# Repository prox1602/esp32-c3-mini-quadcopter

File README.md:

# ESP32-C3 Mini Quadcopter

> **Project Status: Work in Progress**  
> Custom PCB (Rev 1.0), 3D-printed airframe, and final hardware assembly are complete. Firmware development is currently paused halfway through to finalize the ESP-NOW communication protocol with the custom handheld controller.

A lightweight, custom-built mini quadcopter engineered from scratch — covering KiCad PCB design, discrete MOSFET motor drivers, 3D-printed mechanics, and modular C++ flight firmware built around the **Seeed Studio XIAO ESP32-C3**.

---

## Development Story & Design Goals

The primary goal of this project was simple: **design a compact, custom-built quadcopter from the ground up and get it flying**, moving beyond off-the-shelf flight controllers into custom PCB design and ECAD–MCAD integration.

* **Scope & MCU Trade-off:** Early in the concept phase, I considered adding a small onboard camera for video recording. However, because the **ESP32-C3** is a single-core RISC-V microcontroller, handling real-time flight stabilization alongside video streaming/recording would compromise control loop reliability. I deliberately narrowed the scope to focus purely on flight control and low-latency wireless communication via **ESP-NOW**.
* **ECAD–MCAD Workflow:** This was my first project integrating a custom KiCad board directly into an Autodesk Inventor mechanical assembly (`cad/drone_assembly.stp`) to verify mounting clearances, motor spacing, wire routing channels, and canopy fit before 3D printing.

---

## Hardware Architecture & Bill of Materials

The propulsion stage uses four discrete low-side N-channel MOSFET switches integrated directly onto the custom PCB. Each channel includes an **SS14** Schottky flyback diode to suppress inductive voltage spikes and a **10 kΩ** gate pull-down resistor to prevent unintended motor spin-up during boot. A **470 µF** bulk electrolytic capacitor sits across the battery rail to mitigate voltage sag under load.

| Component | Specification | Qty | Role |
| :--- | :--- | :---: | :--- |
| **Microcontroller** | Seeed Studio XIAO ESP32-C3 (RISC-V, 3.3V) | 1 | Flight controller & ESP-NOW wireless link |
| **IMU Sensor** | GY-BMI160 (6-axis accel + gyro, I2C) | 1 | Attitude and angular rate estimation |
| **Motors** | 8520 Coreless Brushed DC (8.5 × 20 mm, CW/CCW) | 4 | Quadcopter propulsion |
| **Motor Drivers** | AO3400A N-MOSFET (SOT-23, 30V / 5.8A, 1.4W) | 4 | Logic-level PWM motor switching |
| **Flyback Protection** | SS14 Schottky Diode (SMB package) | 4 | Inductive spike suppression across motors |
| **Gate Pull-downs** | 10 kΩ Resistors (`R1`–`R4`) | 4 | Keep MOSFET gates low during MCU reset |
| **Bulk Decoupling** | 470 µF Electrolytic Capacitor (`C1`) | 1 | Stabilize 1S LiPo rail during current spikes |
| **Battery** | 1S LiPo 3.7V 600 mAh (30C discharge) | 1 | Main power supply |
| **Airframe & Canopy** | Custom 3D-printed frame & electronics cover | 1 set | Mechanical structure & PCB protection |

---

## Rev 1.0 Errata & Lessons Learned

This board is my **first custom PCB designed in KiCad**. Bringing up Rev 1.0 surfaced three real-world hardware issues that taught me a lot about moving from schematic to physical hardware:

1. **SOT-23 MOSFET Pinout Mismatch:**  
   Using default KiCad MOSFET footprints resulted in a pinout mismatch against the actual AO3400A SOT-23 datasheet. Rather than stalling the project for a second PCB spin, I manually reworked the board by soldering the transistors inverted and angled to match the required Gate–Drain–Source routing.
2. **SMD vs. THT Resistor Sourcing:**  
   The PCB was laid out with 0805 SMD resistor pads (`R1`–`R4`), but due to small-batch component sourcing and shipping costs, standard through-hole (THT) 10 kΩ resistors were adapted and soldered directly onto the SMD pads (visible on the assembled PCB photo above).
3. **Power Rail Conflict (`VBUS` vs. `VBAT`):**  
   In Rev 1.0, the 1S LiPo rail (`+BATT`) was routed to the XIAO's `VBUS` pin (5V USB rail) instead of the dedicated `VBAT` pad. **Hardware constraint:** USB-C and the LiPo battery must *never* be connected simultaneously on Rev 1.0 to avoid back-feeding 5V into the 3.7–4.2V LiPo cell.

**Key Takeaways for Rev 2.0:**
* Always verify physical component datasheets directly against KiCad symbol-to-footprint pin mappings before generating Gerbers.
* Finalize the BOM before locking package sizes.
* Route battery power strictly to `VBAT` (or add proper power-path isolation) and add 100–220 Ω series gate resistors between the ESP32 GPIO pins and MOSFET gates.

---

## Software Architecture

The firmware is developed in **PlatformIO** (C++ / Arduino framework) on top of my custom modular framework — [**Robot Management System (RMS)**](https://github.com/prox1602/Robot-Management-System).

Instead of a monolithic `loop()`, responsibilities are split into decoupled classes inheriting from `IController`. Each controller automatically registers itself with the singleton `DeviceController` upon instantiation and implements its own `setup()` and `update()` lifecycle methods. Data is exchanged asynchronously without direct class coupling via RMS primitives (`Service`, `Buffer`, `DataBase`):

* **IMU & Attitude Controller:** Interfaces with the GY-BMI160 over I2C (`DFRobot_BMI160`) and computes orientation angles.
* **ESP-NOW Communication Controller:** Manages wireless packet reception and telemetry exchange with the handheld controller.
* **Flight / Motor Controller:** Consumes attitude feedback and target setpoints to drive the 4-channel PWM MOSFET outputs.

---

## Development Progress

### Completed
* Custom PCB schematic, layout (KiCad), assembly, and Rev 1.0 hardware rework.
* 3D-printed airframe, protective canopy, motor wiring, and full ECAD–MCAD assembly.
* Core firmware architecture using RMS (IMU reading, motor driver setup, initial ESP-NOW structure).

### In Progress / Next Steps
* Finalizing the ESP-NOW packet structure and handshake protocol with the custom controller.
* Completing the flight stabilization loop (sensor filtering, PID tuning, and motor mixing).
* Bench thrust tests and maiden flight.

---

## Repository Structure

```text
├── pcb/        # KiCad project, schematic, PCB layout, and board 3D STEP model
├── cad/        # 3D-printed frame, canopy, and full drone assembly (.stp)
├── code/       # PlatformIO project and WIP ESP32-C3 firmware
├── assets/     # Build photos and media
└── LICENSE     # MIT License

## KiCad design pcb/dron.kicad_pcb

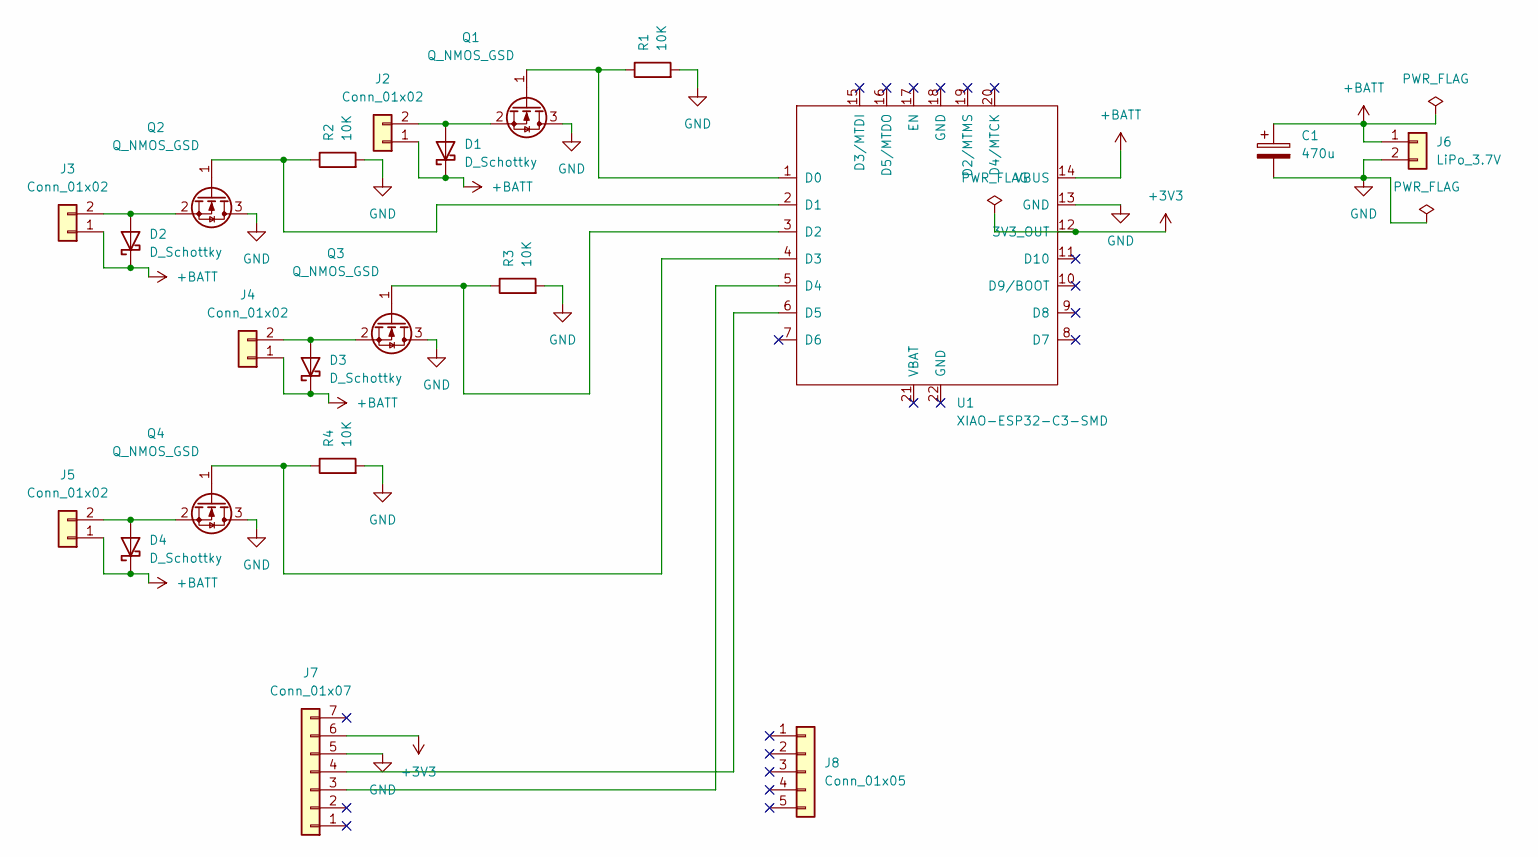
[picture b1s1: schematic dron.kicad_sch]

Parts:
C1: 470u; CP_Radial_D6.3mm_P2.50mm
D1, D2, D3, D4: D_Schottky; D_SMB_Handsoldering
J2, J3, J4, J5: Conn_01x02; PinHeader_1x02_P2.54mm_Vertical
J6: LiPo_3.7V; PinHeader_1x02_P2.54mm_Vertical
J7: Conn_01x07; PinHeader_1x07_P2.54mm_Vertical
J8: Conn_01x05; PinHeader_1x05_P2.54mm_Vertical
Q1, Q2, Q3, Q4: Q_NMOS_GSD; SOT-23
R1, R2, R3, R4: 10K; R_0805_2012Metric
U1: XIAO-ESP32-C3-SMD; XIAO-ESP32-C3-DIP-SMD

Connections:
+3V3: J7.6, U1.12 (3V3_OUT)
+BATT: C1.1, D1.1 (K), D2.1 (K), D3.1 (K), D4.1 (K), J2.1, J3.1, J4.1, J5.1, J6.1, U1.14 (VBUS)
GND: C1.2, J6.2, J7.5, Q1.3 (D), Q2.3 (D), Q3.3 (D), Q4.3 (D), R1.2, R2.2, R3.2, R4.2, U1.13 (GND)
unnamed: D1.2 (A), J2.2, Q1.2 (S)
unnamed: D2.2 (A), J3.2, Q2.2 (S)
unnamed: D3.2 (A), J4.2, Q3.2 (S)
unnamed: D4.2 (A), J5.2, Q4.2 (S)
unnamed: J7.3, U1.5 (D4)
unnamed: J7.4, U1.6 (D5)
unnamed: Q1.1 (G), R1.1, U1.1 (D0)
unnamed: Q2.1 (G), R2.1, U1.2 (D1)
unnamed: Q3.1 (G), R3.1, U1.3 (D2)
unnamed: Q4.1 (G), R4.1, U1.4 (D3)

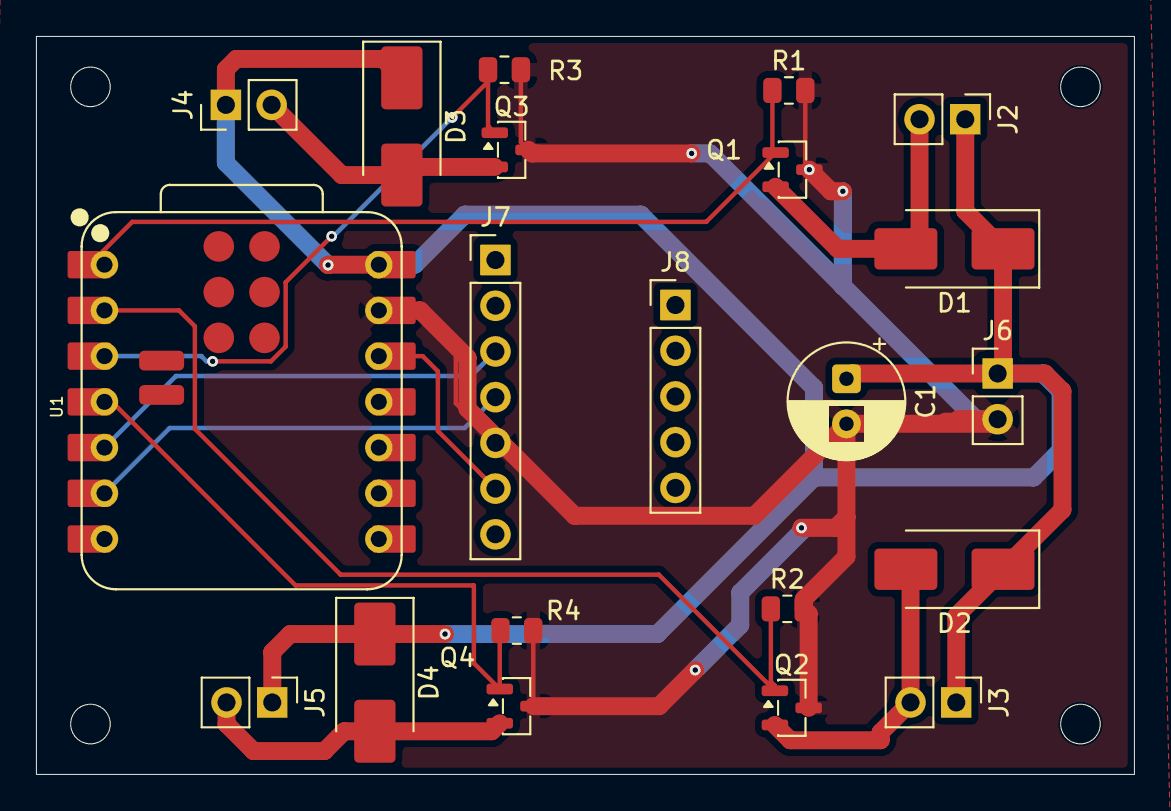
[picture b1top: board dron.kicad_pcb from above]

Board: 2 copper layers, 61.0 x 41.0 mm, 21 parts (0 on the bottom side), 13 nets.
